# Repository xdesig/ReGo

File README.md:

# Rego

> [!NOTE]
> Docu in Galician language

Controlador/programador de rego con varias saidas e entradas de sensado

## [Versión 0V3.][ReGo0v3]

Na versión 3 utilizase un Arduino ProMicro, Ten dúas entradas para sensores de humidade, un DTH11 para sensar a humidade e temperatura ambiental permite controlar oito saídas mediante Mosfets en surtidor común. Conta con un RTC PCF8523T e comunicacións USB e I2C

## [Versión 0V401.][ReGo0v4]

Aqui xa temos un ESP-WROOM-32, con comunicación WiFi, ten unha pantalla oled 128x64 pix, unha botoeira analóxica de cinco pulsadores, catro entradas para sensores capacitivos, dúas entradas activas a nivel alto e dúas entradas activas a nivel baixo, que poden ser usadas como finais de carreira para fiestras... ou para outos fins, conta con entrada para sensores tipo DHT11
ten un RTC PCF8523T, catro saídas a SSR (Mosfet) de 1A/30V ac ou DC adicadas xeralmente a activar as electrovalvulas ten tamén dúas saídas en surtidor común 2A/30V (por exemplo para controlar os motoes das fiestras).

* ###  Deseñado en Estrimia con agarimo.

## Author and license
* Author: [XDeSIG][TWI01]
* License: [CERN Open Hardware Licence Version 2 - Weakly Reciprocal][CERN-OHL-W]

* Certification: [OSHWA UID ES000038][OSHWA]

* ### To buy boards

Developer don't produce boards to sell. Under [_provider_][provider]
directory there are instructions to order yourself.

<!-- links -->
[ReGo0v3]: https://github.com/xdesig/ReGo/tree/master/ReGo_v3
[ReGo0v4]: https://github.com/xdesig/ReGo/tree/master/ReGo_V4

[CERN-OHL-W]: https://ohwr.org/cern_ohl_w_v2.pdf
[TWI01]: https://twitter.com/xdesig
[provider]: https://www.pcbway.com/project/shareproject/Controlador_de_ReGo_V401_bd0da5d6.html
[OSHWA]: https://certification.oshwa.org/es000038.html

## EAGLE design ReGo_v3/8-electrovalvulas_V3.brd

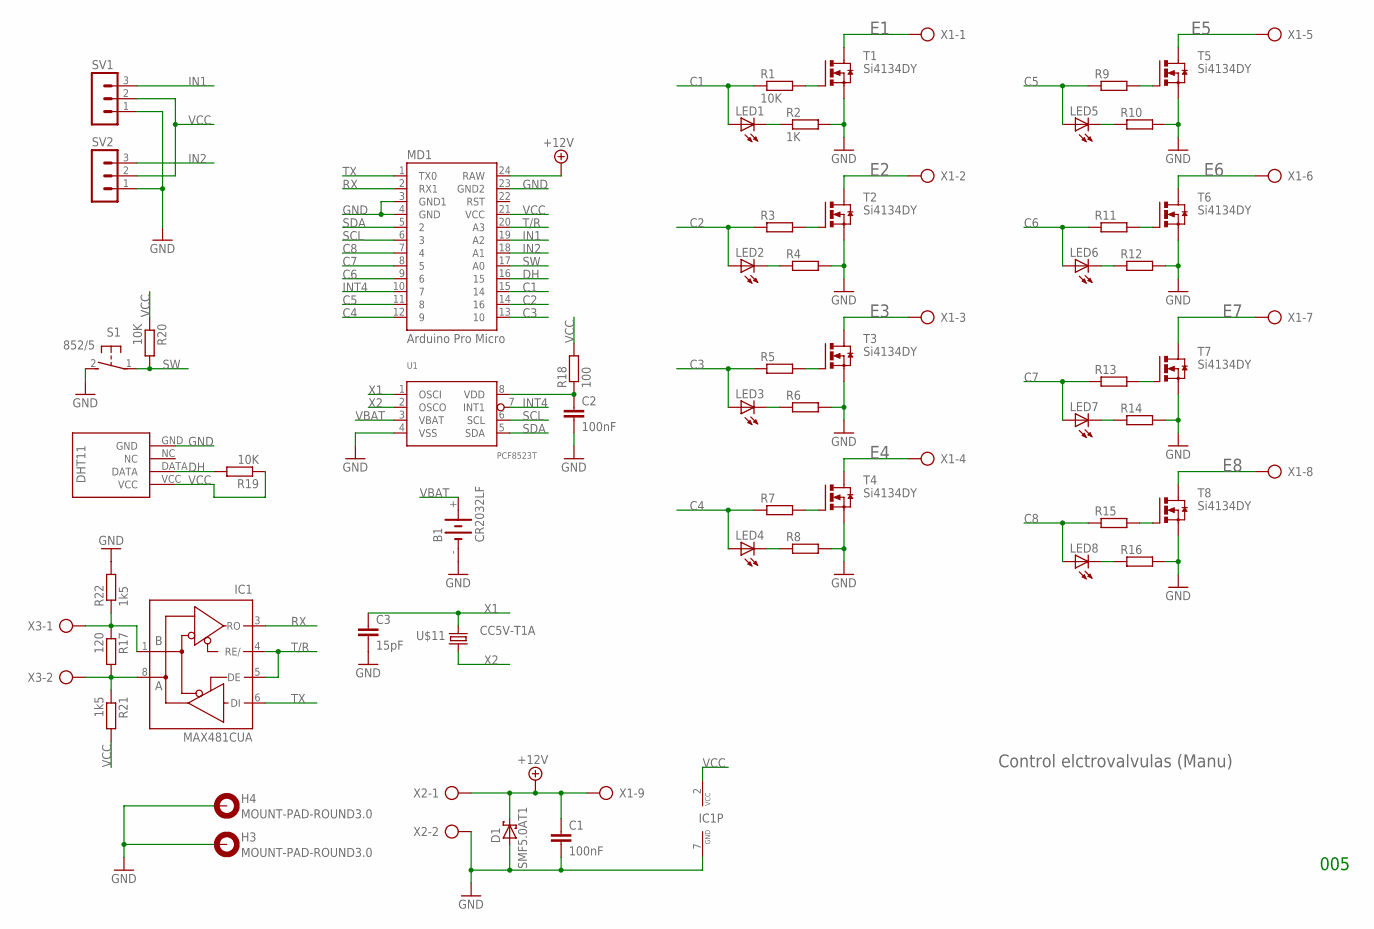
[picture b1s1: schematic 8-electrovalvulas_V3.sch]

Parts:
B1: CR2032LF; BATTERY_1236_C
C1: 100nF; C1206
C2: 100nF; C0603
C3: 15pF; C0603
D1: SMF5.0AT1; SOD123FL
H3, H4: MOUNT-PAD-ROUND3.0; 3,0-PAD
IC1: MAX481CUA; UMAX8
IC10: DHT11-PION.
LED1, LED2, LED3, LED4, LED5, LED6, LED7, LED8: LEDSML0805; SML0805
MD1: Arduino Pro Micro; PRO_MICRO
R1, R19, R20: 10K; R0603
R2: 1K; R0603
R3, R4, R5, R6, R7, R8, R9, R10, R11, R12, R13, R14, R15, R16: R-EU_R0603; R0603
R17: 120; R0603
R18: 100; R0603
R21, R22: 1k5; R0603
S1: 852/5; B3F-31XX
SV1, SV2: MA03-1
T1, T2, T3, T4, T5, T6, T7, T8: Si4134DY; SO-08
U1: PCF8523T; SOT96-1
U$11: CC5V-T1A; T1A
X1: AK300/9
X2, X3: AK300/2

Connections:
+12V: C1.1, D1.C, MD1.24 (RAW), X1.9, X2.1
A: IC1.8 (A), R17.2, R21.1, X3.2
B: IC1.1 (B), R17.1, R22.1, X3.1
C1: LED1.A, MD1.15 (14), R1.1
C2: LED2.A, MD1.14 (16), R3.1
C3: LED3.A, MD1.13 (10), R5.1
C4: LED4.A, MD1.12 (9), R7.1
C5: LED5.A, MD1.11 (8), R9.1
C6: LED6.A, MD1.9 (6), R11.1
C7: LED7.A, MD1.8 (5), R13.1
C8: LED8.A, MD1.7 (4), R15.1
DH: IC10.DATA, MD1.16 (15), R19.2
E1: T1.5 (D), T1.6 (D), T1.7 (D), T1.8 (D), X1.1
E2: T2.5 (D), T2.6 (D), T2.7 (D), T2.8 (D), X1.2
E3: T3.5 (D), T3.6 (D), T3.7 (D), T3.8 (D), X1.3
E4: T4.5 (D), T4.6 (D), T4.7 (D), T4.8 (D), X1.4
E5: T5.5 (D), T5.6 (D), T5.7 (D), T5.8 (D), X1.5
E6: T6.5 (D), T6.6 (D), T6.7 (D), T6.8 (D), X1.6
E7: T7.5 (D), T7.6 (D), T7.7 (D), T7.8 (D), X1.7
E8: T8.5 (D), T8.6 (D), T8.7 (D), T8.8 (D), X1.8
GND: B1.-, C1.2, C2.2, C3.2, D1.A, H3.B3,0, H4.B3,0, IC1.7 (GND), IC10.GND, MD1.3 (GND1), MD1.4 (GND), MD1.23 (GND2), R2.2, R4.2, R6.2, R8.2, R10.2, R12.2, R14.2, R16.2, R22.2, S1.2 (S), SV1.1, SV2.1, T1.1 (S), T1.2 (S), T1.3 (S), T2.1 (S), T2.2 (S), T2.3 (S), T3.1 (S), T3.2 (S), T3.3 (S), T4.1 (S), T4.2 (S), T4.3 (S), T5.1 (S), T5.2 (S), T5.3 (S), T6.1 (S), T6.2 (S), T6.3 (S), T7.1 (S), T7.2 (S), T7.3 (S), T8.1 (S), T8.2 (S), T8.3 (S), U1.4 (VSS), X2.2
IN1: MD1.19 (A2), SV1.3
IN2: MD1.18 (A1), SV2.3
INT4: MD1.10 (7), U1.7 (INT1)
unnamed: R1.2, T1.4 (G)
unnamed: LED1.C, R2.1
unnamed: R3.2, T2.4 (G)
unnamed: C2.1, R18.1, U1.8 (VDD)
unnamed: LED2.C, R4.1
unnamed: R5.2, T3.4 (G)
unnamed: LED3.C, R6.1
unnamed: R7.2, T4.4 (G)
unnamed: R9.2, T5.4 (G)
unnamed: LED4.C, R8.1
unnamed: LED5.C, R10.1
unnamed: R11.2, T6.4 (G)
unnamed: LED6.C, R12.1
unnamed: R13.2, T7.4 (G)
unnamed: LED7.C, R14.1
unnamed: R15.2, T8.4 (G)
unnamed: LED8.C, R16.1
RX: IC1.3 (RO), MD1.2 (RX1)
SCL: MD1.6 (3), U1.6 (SCL)
SDA: MD1.5 (2), U1.5 (SDA)
SW: MD1.17 (A0), R20.2, S1.1
T/R: IC1.4 (RE/), IC1.5 (DE), MD1.20 (A3)
TX: IC1.6 (DI), MD1.1 (TX0)
VBAT: B1.+, U1.3 (VBAT)
VCC: IC1.2 (VCC), IC10.VCC, MD1.21 (VCC), R18.2, R19.1, R20.1, R21.2, SV1.2, SV2.2
X1: C3.1, U1.1 (OSCI), U$11.2
X2: U1.2 (OSCO), U$11.1

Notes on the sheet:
Control elctrovalvulas (Manu)
005

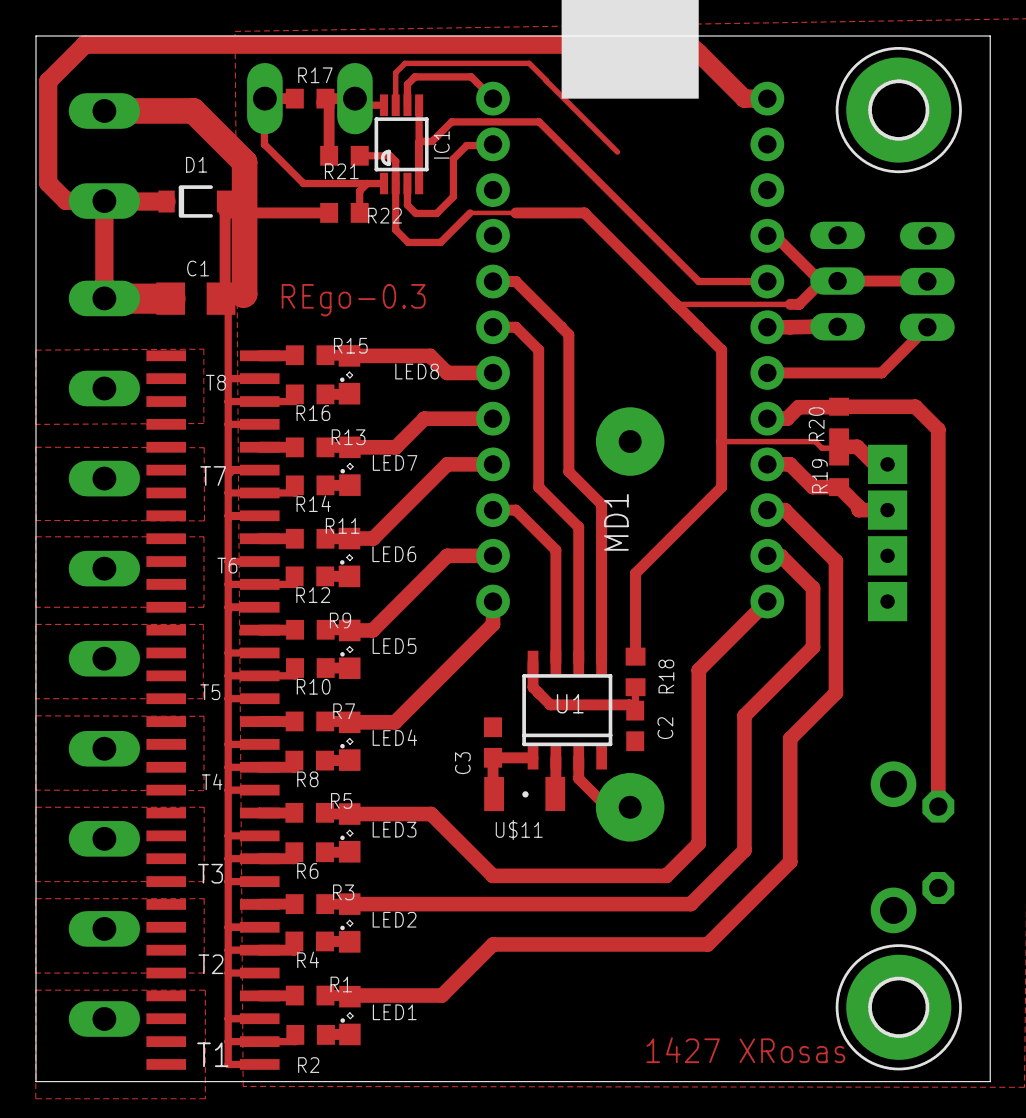
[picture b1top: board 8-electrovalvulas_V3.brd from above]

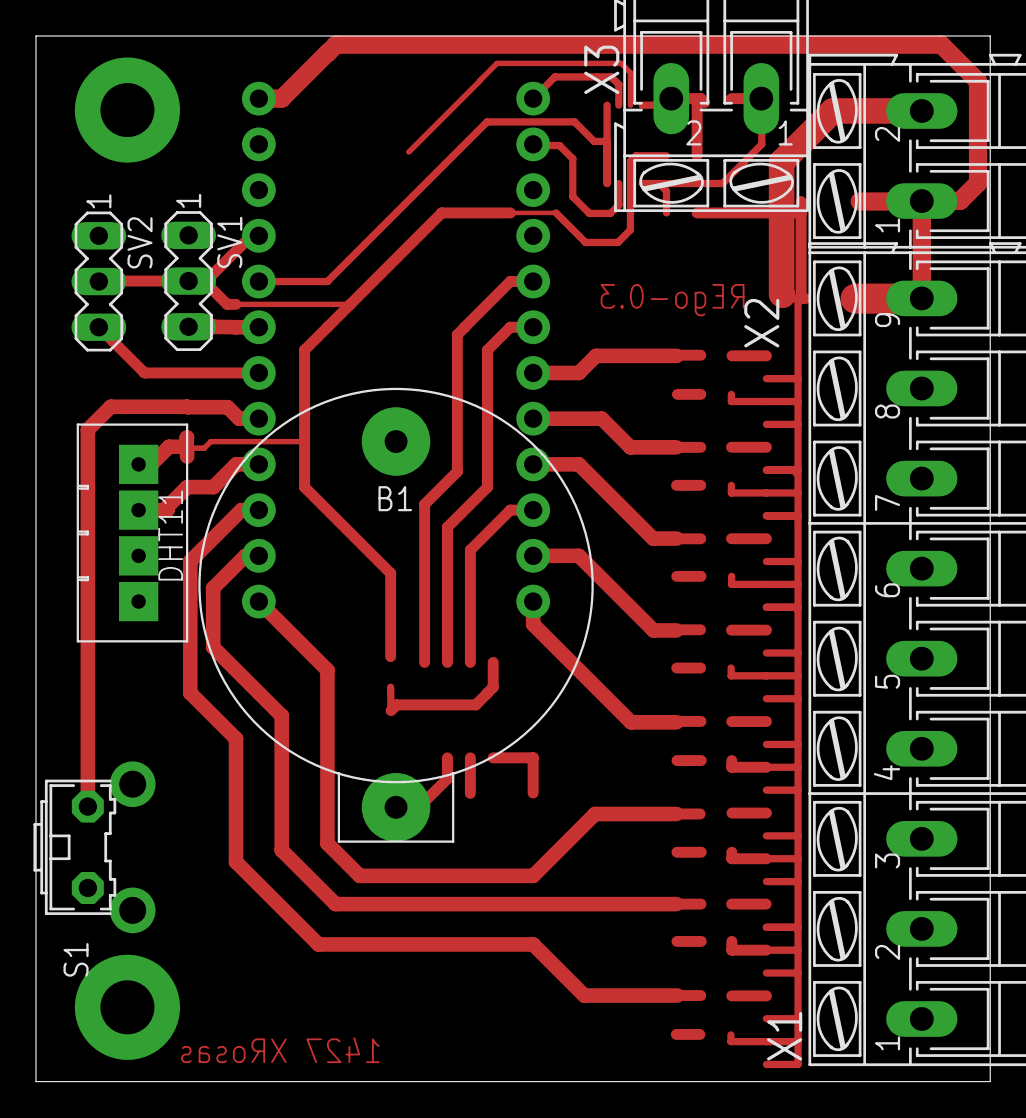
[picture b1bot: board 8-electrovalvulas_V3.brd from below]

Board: 2 copper layers, 53.0 x 58.1 mm, 56 parts (8 on the bottom side), 51 nets.

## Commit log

2015-06-19 :circus_tent: Added .gitattributes & .gitignore files
2015-06-19 Inicio
2022-12-08 rename
2023-09-18 Update certification
